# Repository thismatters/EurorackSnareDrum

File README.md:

# Snare Drum

The circuit here is an implementation the circuit in the [Moritz Klien snare drum video](https://www.youtube.com/watch?v=hULEn2_4Unw) with all the trappings to make it a proper module. I recommend that video completely, please watch it. The circuit has 5 knobs, but I've limited myself to 4 knobs: Decay, Attack, Tone, and Pitch. The other knob is present as a screw-turn potentiometers accessible from the front panel for tuning Snappy.

The KiCAD project here uses the library/footprints [found in my companion repo](https://github.com/thismatters/EurorackKiCAD).

## Width

6hp on a standard 3U rack.

## Inputs

4 Jacks
- Gate
- Accent CV
- Snappy CV
- Pitch CV

4 Knobs:
- Decay
- Attack
- Tone
- Pitch

1 Screw Pot (accessible from front):
- Snappy

## Outputs

1 Jack for audio output.

## Vendors

There are part numbers in the [BOM](snare-drum.csv) for many of the parts (not for basic passives though) at the following vendors:

* [Mouser](https://www.mouser.com): Needs no introduction. Get your ICs from here (or [digikey](https://www.digikey.com)).
* [Tayda Electronics](https://www.taydaelectronics.com/): Good supplier for passive components; audio jacks, and potentiometers. Their audio jacks are slightly smaller than the thonkiconn from thonk.
* [Love My Switches](https://lovemyswitches.com/): Has [really good knobs](https://lovemyswitches.com/anodized-aluminum-knob-the-lo-fi-1-4-smooth-shaft-12-5mm-od/) to go on those potentiometers!
* [OSHPark](https://oshpark.com/): Fast and (relatively) cheap PCB manufacturer. Prototype run pending.

## Changelog

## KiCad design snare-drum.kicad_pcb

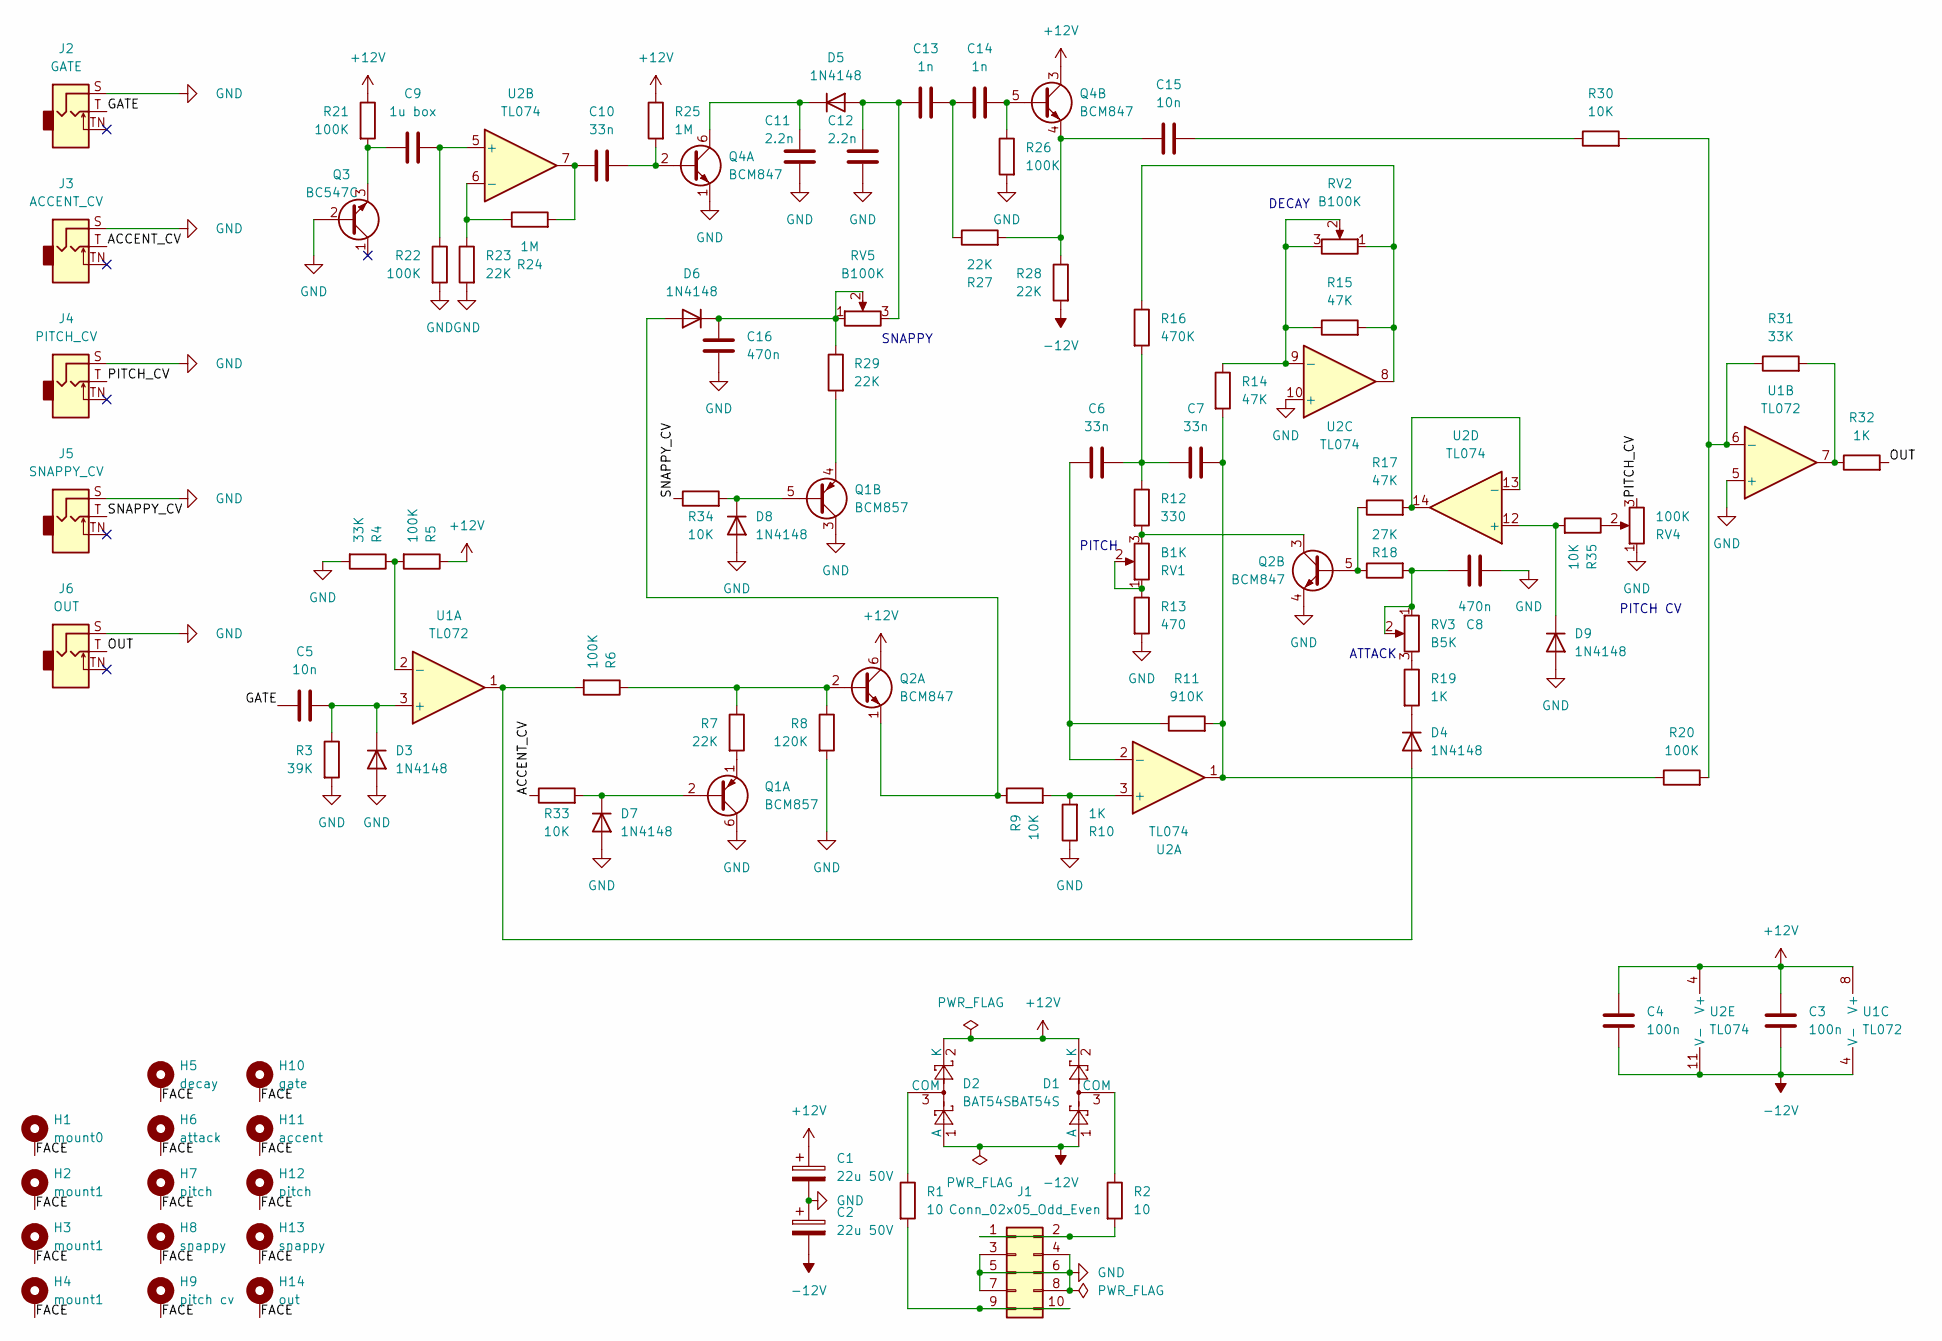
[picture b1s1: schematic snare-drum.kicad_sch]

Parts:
C1, C2: 22u 50V; CP_Radial_D5.0mm_P2.50mm
C3, C4: 100n; C_0805_2012Metric
C5, C15: 10n; C_0805_2012Metric
C6, C7, C10: 33n; C_0805_2012Metric
C8, C16: 470n; C_0805_2012Metric
C9: 1u box; C_Rect_L7.2mm_W7.2mm_P5.00mm_FKS2_FKP2_MKS2_MKP2
C11, C12: 2.2n; C_0805_2012Metric
C13, C14: 1n; C_0805_2012Metric
D1, D2: BAT54S; SOT-23; PartNum 863-BAT54SLT1G
D3, D4, D5, D6, D7, D8, D9: 1N4148; D_SOD-323_HandSoldering
H1: mount0; Mech-MountingHole
H2, H3, H4: mount1; Mech-MountingHole
H5: decay; Mech-Potentiometer-Hole_level
H6: attack; Mech-Potentiometer-Hole_level
H7: pitch; Mech-Potentiometer-Hole_level
H8: snappy; Mech-Potentiometer-Hole_level
H9: pitch cv; Mech-LED-Hole-3mm
H10: gate; Mech-AudioJack-Hole-Input-Gate
H11: accent; Mech-AudioJack-Hole-Input-CV
H12: pitch; Mech-AudioJack-Hole-Input-CV
H13: snappy; Mech-AudioJack-Hole-Input-CV
H14: out; Mech-AudioJack-Hole-Output
J1: Conn_02x05_Odd_Even; PinHeader_2x05_P2.54mm_Vertical; PartNum A-2939
J2: GATE; AudioJack2_Tayda_A-2566; PartNum A-2566
J3: ACCENT_CV; AudioJack2_Tayda_A-2566; PartNum A-2566
J4: PITCH_CV; AudioJack2_Tayda_A-2566; PartNum A-2566
J5: SNAPPY_CV; AudioJack2_Tayda_A-2566; PartNum A-2566
J6: OUT; AudioJack2_Tayda_A-2566; PartNum A-2566
Q1: BCM857; TSOP-6_1.65x3.05mm_P0.95mm; PartNum 771-BCM857DS135
Q2, Q4: BCM847; TSOP-6_1.65x3.05mm_P0.95mm; PartNum 771-BCM847DS135
Q3: BC547C; TO-92_Inline_Wide
R1, R2: 10; R_0805_2012Metric
R3: 39K; R_0805_2012Metric
R4, R31: 33K; R_0805_2012Metric
R5, R6, R20, R21, R22, R26: 100K; R_0805_2012Metric
R7, R23, R27, R28, R29: 22K; R_0805_2012Metric
R8: 120K; R_0805_2012Metric
R9, R30, R33, R34, R35: 10K; R_0805_2012Metric
R10, R19, R32: 1K; R_0805_2012Metric
R11: 910K; R_0805_2012Metric
R12: 330; R_0805_2012Metric
R13: 470; R_0805_2012Metric
R14, R15, R17: 47K; R_0805_2012Metric
R16: 470K; R_0805_2012Metric
R18: 27K; R_0805_2012Metric
R24, R25: 1M; R_0805_2012Metric
RV1: B1K; Potentiometer_RV16AF-41-15R1
RV2, RV5: B100K; Potentiometer_RV16AF-41-15R1
RV3: B5K; Potentiometer_RV16AF-41-15R1
RV4: 100K; Potentiometer_Bourns_3296W_Vertical
U1: TL072; SOIC-8_3.9x4.9mm_P1.27mm; PartNum 595-TL072CDR
U2: TL074; SO-14_3.9x8.65mm_P1.27mm; PartNum 595-TL074CDR

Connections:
+12V: C1.1, C3.1, C4.1, D1.2 (K), D2.2 (K), Q2.6 (C1), Q4.3 (C2), R5.1, R21.1, R25.1, U1.8 (V+), U2.4 (V+)
-12V: C2.2, C3.2, C4.2, D1.1 (A), D2.1 (A), R28.2, U1.4 (V-), U2.11 (V-)
/ACCENT_CV: J3.T, R33.1
/FACE: H1.1 (1_1), H2.1 (1_1), H3.1 (1_1), H4.1 (1_1), H5.1 (1_1), H6.1 (1_1), H7.1 (1_1), H8.1 (1_1), H9.1 (1_1), H10.1 (1_1), H11.1 (1_1), H12.1 (1_1), H13.1 (1_1), H14.1 (1_1)
/GATE: C5.1, J2.T
/OUT: J6.T, R32.2
/PITCH_CV: J4.T, RV4.3
/SNAPPY_CV: J5.T, R34.1
GND: C1.2, C2.1, C8.2, C11.2, C12.2, C16.2, D3.2 (A), D7.2 (A), D8.2 (A), D9.2 (A), J1.3, J1.4, J1.5, J1.6, J1.7, J1.8, J2.S, J3.S, J4.S, J5.S, J6.S, Q1.3 (C2), Q1.6 (C1), Q2.4 (E2), Q3.2 (B), Q4.1 (E1), R3.2, R4.2, R8.2, R10.1, R13.2, R22.2, R23.2, R26.2, RV4.1, U1.5 (+), U2.10 (+)
unnamed: C6.2, C7.1, R12.1, R16.2
unnamed: C7.2, R11.2, R14.2, R20.1, U2.1
unnamed: C8.1, R18.2, RV3.1, RV3.2
unnamed: C10.1, R24.2, U2.7
unnamed: C13.2, C14.1, R27.1
unnamed: C15.2, R30.1
unnamed: D1.3 (COM), R2.1
unnamed: D2.3 (COM), R1.1
unnamed: C5.2, D3.1 (K), R3.1, U1.3 (+)
unnamed: D4.2 (A), R6.2, U1.1
unnamed: D4.1 (K), R19.2
unnamed: C12.1, C13.1, D5.2 (A), RV5.3
unnamed: C11.1, D5.1 (K), Q4.6 (C1)
unnamed: D6.2 (A), Q2.1 (E1), R9.1
unnamed: C16.1, D6.1 (K), R29.1, RV5.1, RV5.2
unnamed: D7.1 (K), Q1.2 (B1), R33.2
unnamed: D8.1 (K), Q1.5 (B2), R34.2
unnamed: D9.1 (K), R35.2, U2.12 (+)
unnamed: J1.1, J1.2, R2.2
unnamed: J1.9, J1.10, R1.2
unnamed: Q1.1 (E1), R7.2
unnamed: Q1.4 (E2), R29.2
unnamed: Q2.2 (B1), R6.1, R7.1, R8.1
unnamed: Q2.5 (B2), R17.1, R18.1
unnamed: Q2.3 (C2), R12.2, RV1.3
unnamed: C9.1, Q3.3 (E), R21.2
unnamed: C10.2, Q4.2 (B1), R25.2
unnamed: C14.2, Q4.5 (B2), R26.1
unnamed: C15.1, Q4.4 (E2), R27.2, R28.1
unnamed: R13.1, RV1.1, RV1.2
unnamed: R15.2, R16.1, RV2.1, U2.8
unnamed: R19.1, RV3.3
unnamed: R31.2, R32.1, U1.7
unnamed: R35.1, RV4.2
unnamed: R4.1, R5.2, U1.2 (-)
unnamed: R20.2, R30.2, R31.1, U1.6 (-)
unnamed: R9.2, R10.2, U2.3 (+)
unnamed: C6.1, R11.1, U2.2 (-)
unnamed: C9.2, R22.1, U2.5 (+)
unnamed: R23.1, R24.1, U2.6 (-)
unnamed: R14.1, R15.1, RV2.2, RV2.3, U2.9 (-)
unnamed: R17.2, U2.13 (-), U2.14

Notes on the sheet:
ATTACK
PITCH CV
PITCH
DECAY
SNAPPY

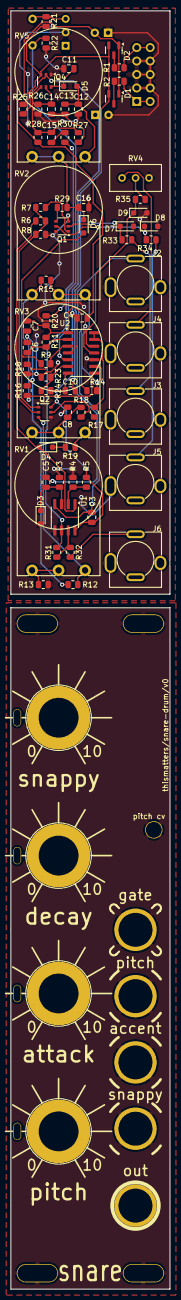
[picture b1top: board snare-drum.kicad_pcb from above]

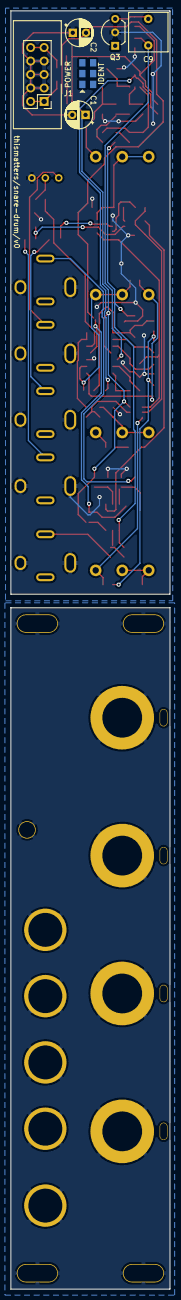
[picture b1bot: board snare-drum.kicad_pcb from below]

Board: 2 copper layers, 30.0 x 241.0 mm, 91 parts (5 on the bottom side), 51 nets.

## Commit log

2026-01-31 fix resistor values
2026-02-01 adding protection to CV inputs
2026-06-06 kicad 10, fixing bom
2026-06-15 v0 ready
2026-06-28 add ident
